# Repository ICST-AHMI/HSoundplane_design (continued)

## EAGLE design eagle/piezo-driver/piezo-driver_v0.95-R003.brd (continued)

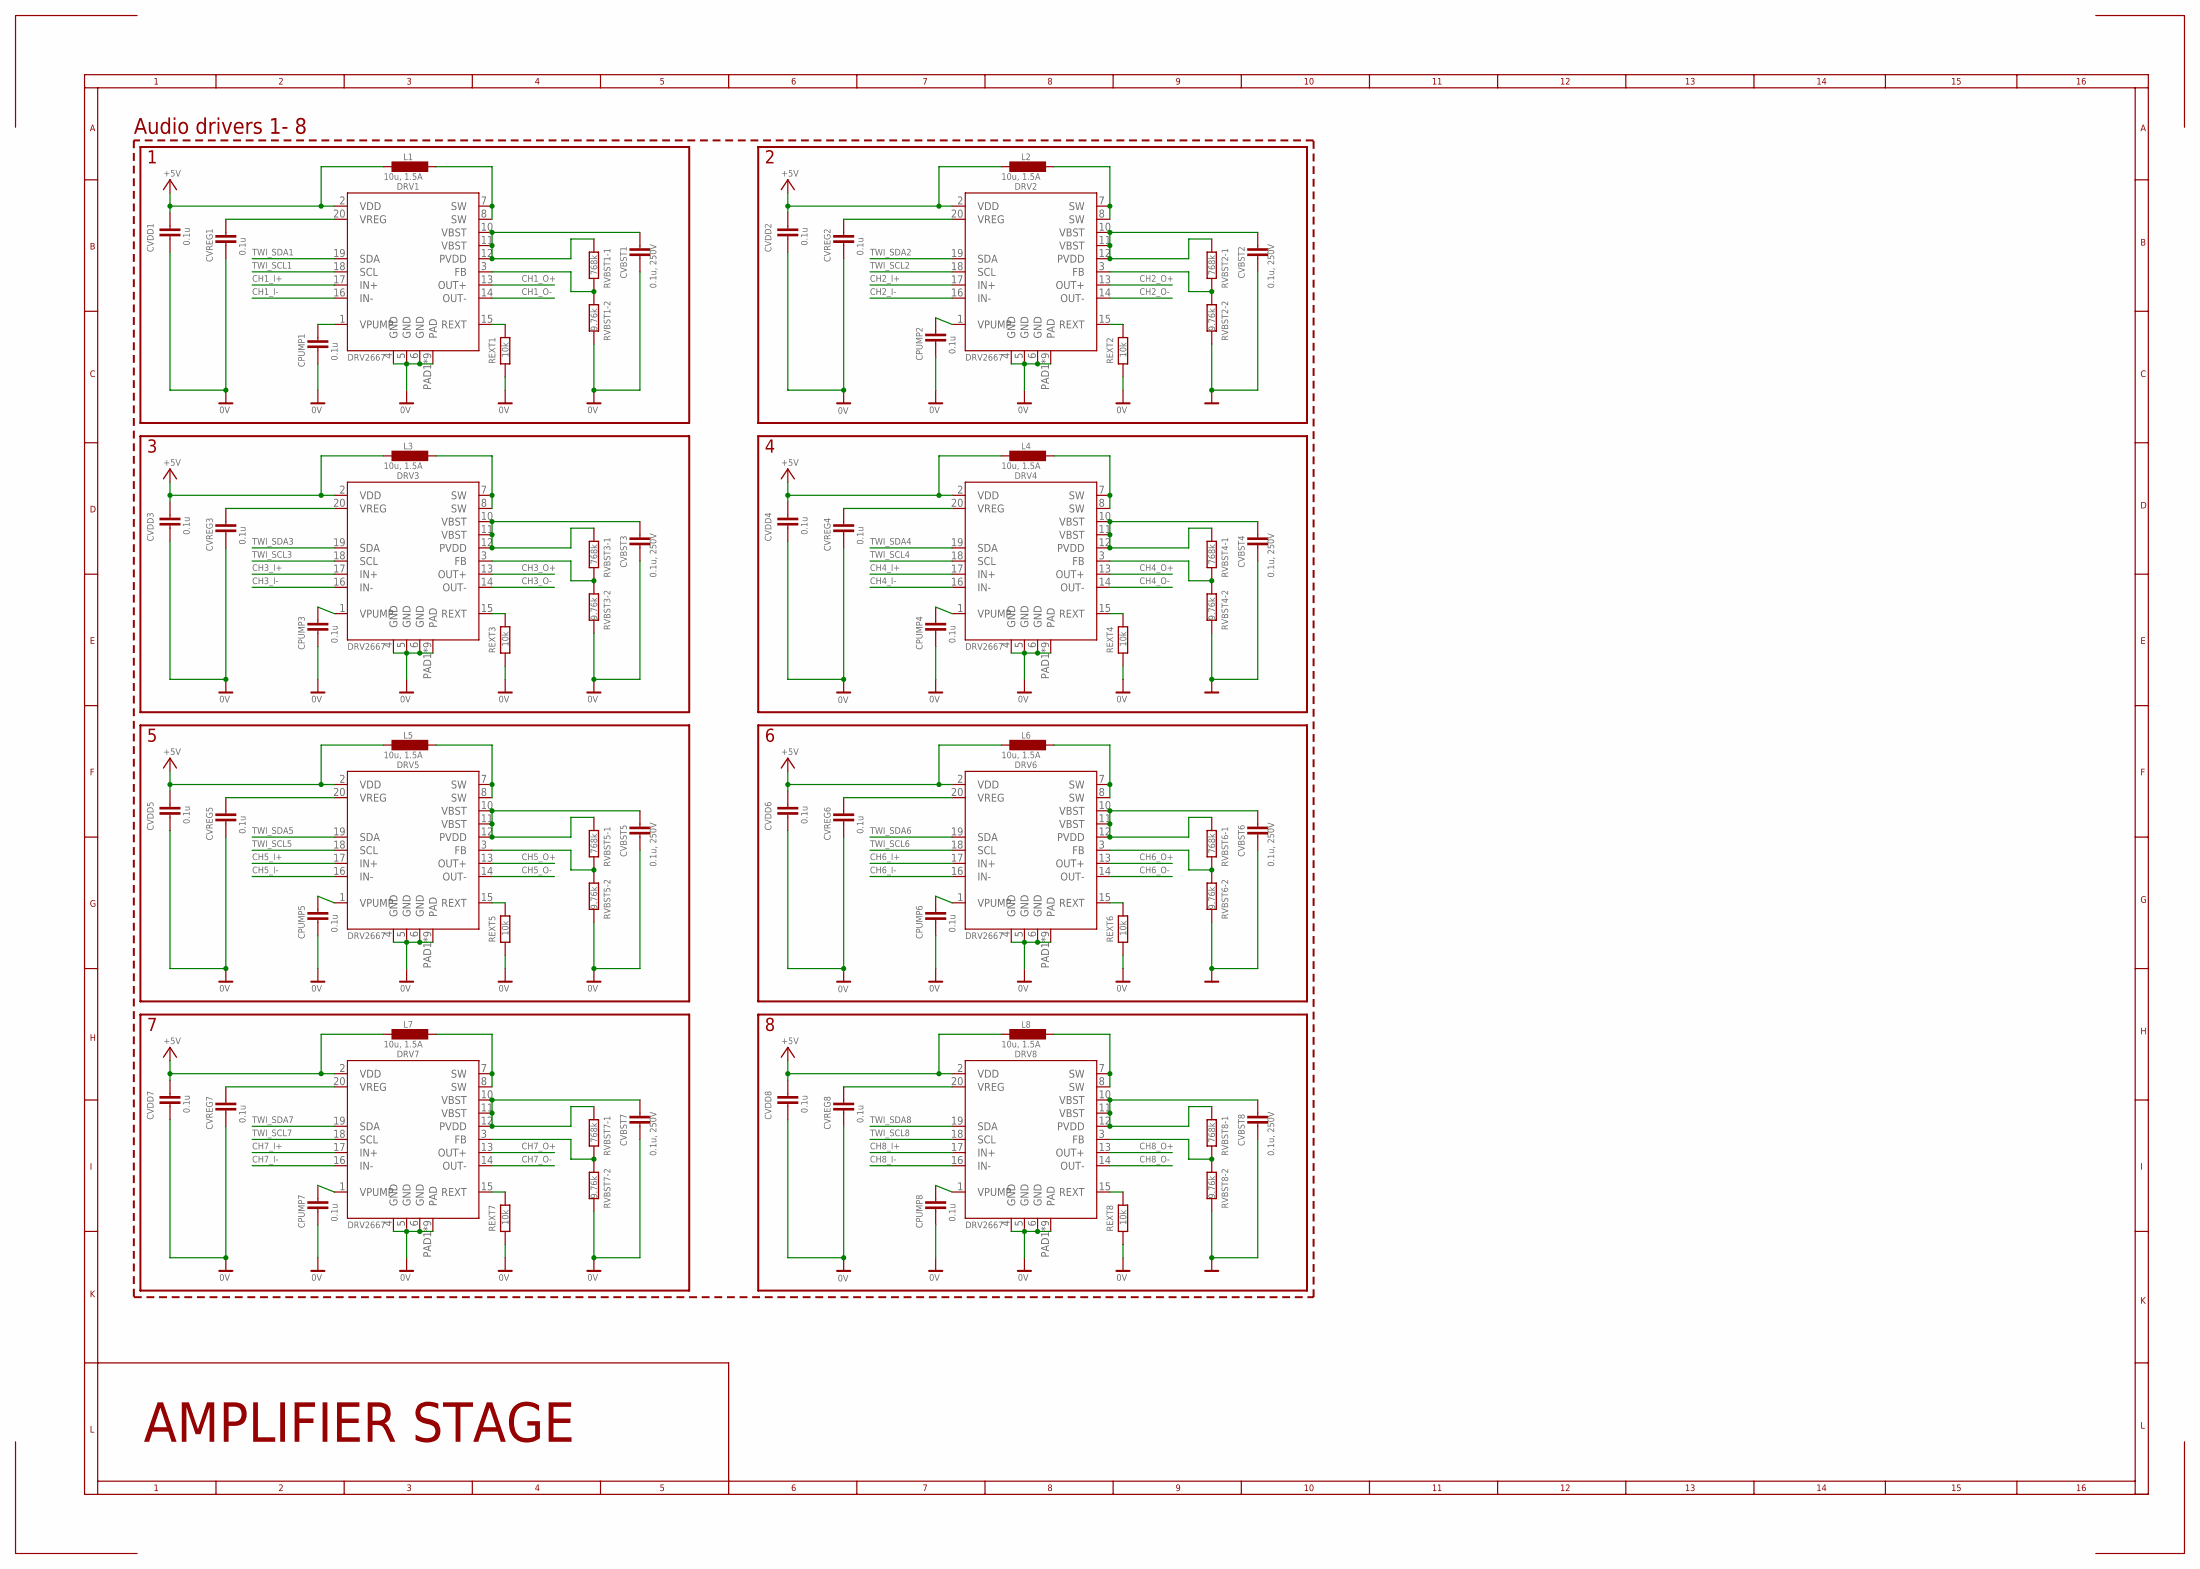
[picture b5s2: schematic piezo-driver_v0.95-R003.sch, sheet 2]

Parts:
CPUMP1, CPUMP2, CPUMP3, CPUMP4, CPUMP5, CPUMP6, CPUMP7, CPUMP8: 0.1u; C0402
CVBST1, CVBST2, CVBST3, CVBST4, CVBST5, CVBST6, CVBST7, CVBST8: 0.1u, 250V; C0805
CVDD1, CVDD2, CVDD3, CVDD4, CVDD5, CVDD6, CVDD7, CVDD8: 0.1u; C0402
CVREG1, CVREG2, CVREG3, CVREG4, CVREG5, CVREG6, CVREG7, CVREG8: 0.1u; C0402
DRV1, DRV2, DRV3, DRV4, DRV5, DRV6, DRV7, DRV8: DRV2667; QFN-20_9TH
L1, L2, L3, L4, L5, L6, L7, L8: 10u, 1.5A; L4.0X4.0
REXT1, REXT2, REXT3, REXT4, REXT5, REXT6, REXT7, REXT8: 10k; R0402
RVBST1-1, RVBST2-1, RVBST3-1, RVBST4-1, RVBST5-1, RVBST6-1, RVBST7-1, RVBST8-1: 768k; R0402
RVBST1-2, RVBST2-2, RVBST3-2, RVBST4-2, RVBST5-2, RVBST6-2, RVBST7-2, RVBST8-2: 9.76k; R0402

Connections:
0V: CPUMP1.2, CPUMP2.2, CPUMP3.2, CPUMP4.2, CPUMP5.2, CPUMP6.2, CPUMP7.2, CPUMP8.2, CVBST1.2, CVBST2.2, CVBST3.2, CVBST4.2, CVBST5.2, CVBST6.2, CVBST7.2, CVBST8.2, CVDD1.2, CVDD2.2, CVDD3.2, CVDD4.2, CVDD5.2, CVDD6.2, CVDD7.2, CVDD8.2, CVREG1.2, CVREG2.2, CVREG3.2, CVREG4.2, CVREG5.2, CVREG6.2, CVREG7.2, CVREG8.2, DRV1.4 (GND), DRV1.5 (GND), DRV1.6 (GND), DRV1.PAD1 (PAD), DRV1.PAD2 (PAD), DRV1.PAD3 (PAD), DRV1.PAD4 (PAD), DRV1.PAD5 (PAD), DRV1.PAD6 (PAD), DRV1.PAD7 (PAD), DRV1.PAD8 (PAD), DRV1.PAD9 (PAD), DRV2.4 (GND), DRV2.5 (GND), DRV2.6 (GND), DRV2.PAD1 (PAD), DRV2.PAD2 (PAD), DRV2.PAD3 (PAD), DRV2.PAD4 (PAD), DRV2.PAD5 (PAD), DRV2.PAD6 (PAD), DRV2.PAD7 (PAD), DRV2.PAD8 (PAD), DRV2.PAD9 (PAD), DRV3.4 (GND), DRV3.5 (GND), DRV3.6 (GND), DRV3.PAD1 (PAD), DRV3.PAD2 (PAD), DRV3.PAD3 (PAD), DRV3.PAD4 (PAD), DRV3.PAD5 (PAD), DRV3.PAD6 (PAD), DRV3.PAD7 (PAD), DRV3.PAD8 (PAD), DRV3.PAD9 (PAD), DRV4.4 (GND), DRV4.5 (GND), DRV4.6 (GND), DRV4.PAD1 (PAD), DRV4.PAD2 (PAD), DRV4.PAD3 (PAD), DRV4.PAD4 (PAD), DRV4.PAD5 (PAD), DRV4.PAD6 (PAD), DRV4.PAD7 (PAD), DRV4.PAD8 (PAD), DRV4.PAD9 (PAD), DRV5.4 (GND), DRV5.5 (GND), DRV5.6 (GND), DRV5.PAD1 (PAD), DRV5.PAD2 (PAD), DRV5.PAD3 (PAD), DRV5.PAD4 (PAD), DRV5.PAD5 (PAD), DRV5.PAD6 (PAD), DRV5.PAD7 (PAD), DRV5.PAD8 (PAD), DRV5.PAD9 (PAD), DRV6.4 (GND), DRV6.5 (GND), DRV6.6 (GND), DRV6.PAD1 (PAD), DRV6.PAD2 (PAD), DRV6.PAD3 (PAD), DRV6.PAD4 (PAD), DRV6.PAD5 (PAD), DRV6.PAD6 (PAD), DRV6.PAD7 (PAD), DRV6.PAD8 (PAD), DRV6.PAD9 (PAD), DRV7.4 (GND), DRV7.5 (GND), DRV7.6 (GND), DRV7.PAD1 (PAD), DRV7.PAD2 (PAD), DRV7.PAD3 (PAD), DRV7.PAD4 (PAD), DRV7.PAD5 (PAD), DRV7.PAD6 (PAD), DRV7.PAD7 (PAD), DRV7.PAD8 (PAD), DRV7.PAD9 (PAD), DRV8.4 (GND), DRV8.5 (GND), DRV8.6 (GND), DRV8.PAD1 (PAD), DRV8.PAD2 (PAD), DRV8.PAD3 (PAD), DRV8.PAD4 (PAD), DRV8.PAD5 (PAD), DRV8.PAD6 (PAD), DRV8.PAD7 (PAD), DRV8.PAD8 (PAD), DRV8.PAD9 (PAD), REXT1.1, REXT2.1, REXT3.1, REXT4.1, REXT5.1, REXT6.1, REXT7.1, REXT8.1, RVBST1-2.1, RVBST2-2.1, RVBST3-2.1, RVBST4-2.1, RVBST5-2.1, RVBST6-2.1, RVBST7-2.1, RVBST8-2.1; also elsewhere on the board
+5V: CVDD1.1, CVDD2.1, CVDD3.1, CVDD4.1, CVDD5.1, CVDD6.1, CVDD7.1, CVDD8.1, DRV1.2 (VDD), DRV2.2 (VDD), DRV3.2 (VDD), DRV4.2 (VDD), DRV5.2 (VDD), DRV6.2 (VDD), DRV7.2 (VDD), DRV8.2 (VDD), L1.2, L2.2, L3.2, L4.2, L5.2, L6.2, L7.2, L8.2; also elsewhere on the board
CH1_I+: DRV1.17 (IN+); also elsewhere on the board
CH1_I-: DRV1.16 (IN-); also elsewhere on the board
CH1_O+: DRV1.13 (OUT+); also elsewhere on the board
CH1_O-: DRV1.14 (OUT-); also elsewhere on the board
CH2_I+: DRV2.17 (IN+); also elsewhere on the board
CH2_I-: DRV2.16 (IN-); also elsewhere on the board
CH2_O+: DRV2.13 (OUT+); also elsewhere on the board
CH2_O-: DRV2.14 (OUT-); also elsewhere on the board
CH3_I+: DRV3.17 (IN+); also elsewhere on the board
CH3_I-: DRV3.16 (IN-); also elsewhere on the board
CH3_O+: DRV3.13 (OUT+); also elsewhere on the board
CH3_O-: DRV3.14 (OUT-); also elsewhere on the board
CH4_I+: DRV4.17 (IN+); also elsewhere on the board
CH4_I-: DRV4.16 (IN-); also elsewhere on the board
CH4_O+: DRV4.13 (OUT+); also elsewhere on the board
CH4_O-: DRV4.14 (OUT-); also elsewhere on the board
CH5_I+: DRV5.17 (IN+); also elsewhere on the board
CH5_I-: DRV5.16 (IN-); also elsewhere on the board
CH5_O+: DRV5.13 (OUT+); also elsewhere on the board
CH5_O-: DRV5.14 (OUT-); also elsewhere on the board
CH6_I+: DRV6.17 (IN+); also elsewhere on the board
CH6_I-: DRV6.16 (IN-); also elsewhere on the board
CH6_O+: DRV6.13 (OUT+); also elsewhere on the board
CH6_O-: DRV6.14 (OUT-); also elsewhere on the board
CH7_I+: DRV7.17 (IN+); also elsewhere on the board
CH7_I-: DRV7.16 (IN-); also elsewhere on the board
CH7_O+: DRV7.13 (OUT+); also elsewhere on the board
CH7_O-: DRV7.14 (OUT-); also elsewhere on the board
CH8_I+: DRV8.17 (IN+); also elsewhere on the board
CH8_I-: DRV8.16 (IN-); also elsewhere on the board
CH8_O+: DRV8.13 (OUT+); also elsewhere on the board
CH8_O-: DRV8.14 (OUT-); also elsewhere on the board
CVBST1: CVBST1.1, DRV1.10 (VBST), DRV1.11 (VBST), DRV1.12 (PVDD), RVBST1-1.2
CVBST2: CVBST2.1, DRV2.10 (VBST), DRV2.11 (VBST), DRV2.12 (PVDD), RVBST2-1.2
CVBST3: CVBST3.1, DRV3.10 (VBST), DRV3.11 (VBST), DRV3.12 (PVDD), RVBST3-1.2
CVBST4: CVBST4.1, DRV4.10 (VBST), DRV4.11 (VBST), DRV4.12 (PVDD), RVBST4-1.2
CVBST5: CVBST5.1, DRV5.10 (VBST), DRV5.11 (VBST), DRV5.12 (PVDD), RVBST5-1.2
CVBST6: CVBST6.1, DRV6.10 (VBST), DRV6.11 (VBST), DRV6.12 (PVDD), RVBST6-1.2
CVBST7: CVBST7.1, DRV7.10 (VBST), DRV7.11 (VBST), DRV7.12 (PVDD), RVBST7-1.2
CVBST8: CVBST8.1, DRV8.10 (VBST), DRV8.11 (VBST), DRV8.12 (PVDD), RVBST8-1.2
L1: DRV1.7 (SW), DRV1.8 (SW), L1.1
L2: DRV2.7 (SW), DRV2.8 (SW), L2.1
L3: DRV3.7 (SW), DRV3.8 (SW), L3.1
L4: DRV4.7 (SW), DRV4.8 (SW), L4.1
L5: DRV5.7 (SW), DRV5.8 (SW), L5.1
L6: DRV6.7 (SW), DRV6.8 (SW), L6.1
L7: DRV7.7 (SW), DRV7.8 (SW), L7.1
L8: DRV8.7 (SW), DRV8.8 (SW), L8.1
unnamed: DRV1.3 (FB), RVBST1-1.1, RVBST1-2.2
unnamed: DRV1.15 (REXT), REXT1.2
unnamed: CPUMP1.1, DRV1.1 (VPUMP)
unnamed: CVREG1.1, DRV1.20 (VREG)
unnamed: DRV3.3 (FB), RVBST3-1.1, RVBST3-2.2
unnamed: DRV3.15 (REXT), REXT3.2
unnamed: CPUMP3.1, DRV3.1 (VPUMP)
unnamed: CVREG3.1, DRV3.20 (VREG)
unnamed: DRV4.3 (FB), RVBST4-1.1, RVBST4-2.2
unnamed: DRV4.15 (REXT), REXT4.2
unnamed: CPUMP4.1, DRV4.1 (VPUMP)
unnamed: CVREG4.1, DRV4.20 (VREG)
unnamed: DRV2.3 (FB), RVBST2-1.1, RVBST2-2.2
unnamed: DRV2.15 (REXT), REXT2.2
unnamed: CPUMP2.1, DRV2.1 (VPUMP)
unnamed: CVREG2.1, DRV2.20 (VREG)
unnamed: DRV5.3 (FB), RVBST5-1.1, RVBST5-2.2
unnamed: DRV5.15 (REXT), REXT5.2
unnamed: CPUMP5.1, DRV5.1 (VPUMP)
unnamed: CVREG5.1, DRV5.20 (VREG)
unnamed: DRV6.3 (FB), RVBST6-1.1, RVBST6-2.2
unnamed: DRV6.15 (REXT), REXT6.2
unnamed: CPUMP6.1, DRV6.1 (VPUMP)
unnamed: CVREG6.1, DRV6.20 (VREG)
unnamed: DRV7.3 (FB), RVBST7-1.1, RVBST7-2.2
unnamed: DRV7.15 (REXT), REXT7.2
unnamed: CPUMP7.1, DRV7.1 (VPUMP)
unnamed: CVREG7.1, DRV7.20 (VREG)
unnamed: DRV8.3 (FB), RVBST8-1.1, RVBST8-2.2
unnamed: DRV8.15 (REXT), REXT8.2
unnamed: CPUMP8.1, DRV8.1 (VPUMP)
unnamed: CVREG8.1, DRV8.20 (VREG)
TWI_SCL1: DRV1.18 (SCL); also elsewhere on the board
TWI_SCL2: DRV2.18 (SCL); also elsewhere on the board
TWI_SCL3: DRV3.18 (SCL); also elsewhere on the board
TWI_SCL4: DRV4.18 (SCL); also elsewhere on the board
TWI_SCL5: DRV5.18 (SCL); also elsewhere on the board
TWI_SCL6: DRV6.18 (SCL); also elsewhere on the board
TWI_SCL7: DRV7.18 (SCL); also elsewhere on the board
TWI_SCL8: DRV8.18 (SCL); also elsewhere on the board
TWI_SDA1: DRV1.19 (SDA); also elsewhere on the board
TWI_SDA2: DRV2.19 (SDA); also elsewhere on the board
TWI_SDA3: DRV3.19 (SDA); also elsewhere on the board
TWI_SDA4: DRV4.19 (SDA); also elsewhere on the board
TWI_SDA5: DRV5.19 (SDA); also elsewhere on the board
TWI_SDA6: DRV6.19 (SDA); also elsewhere on the board
TWI_SDA7: DRV7.19 (SDA); also elsewhere on the board
TWI_SDA8: DRV8.19 (SDA); also elsewhere on the board

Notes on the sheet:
AMPLIFIER STAGE
Audio drivers 1- 8

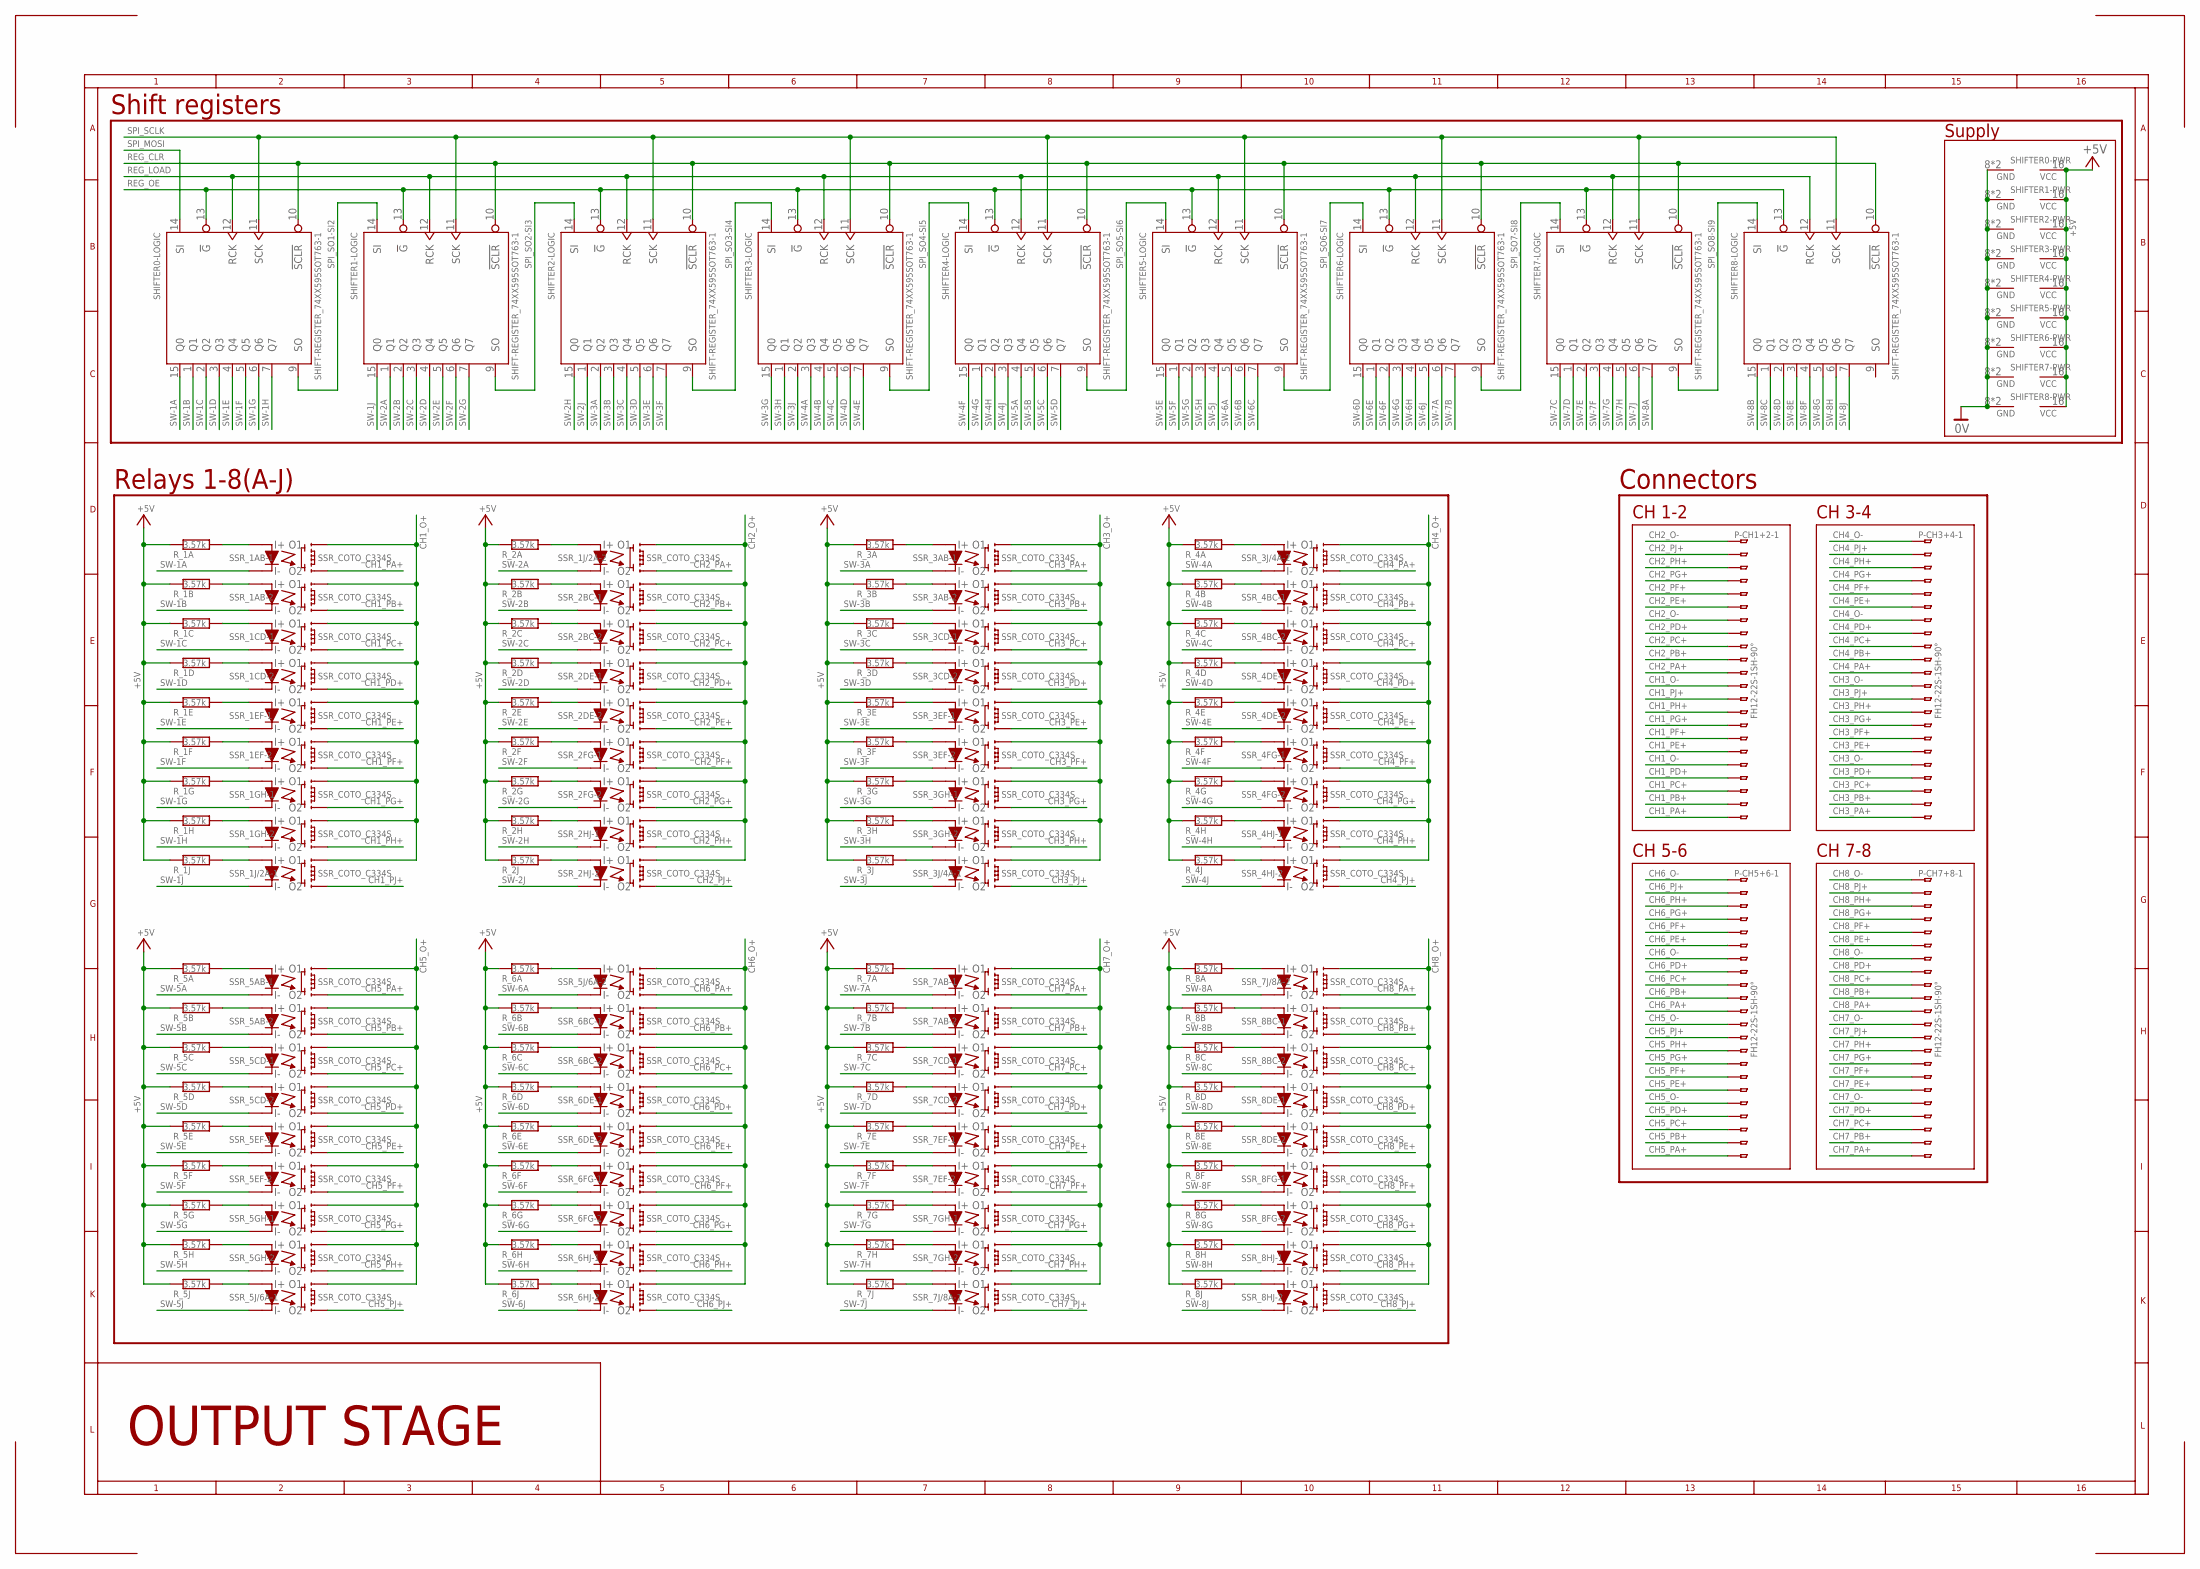
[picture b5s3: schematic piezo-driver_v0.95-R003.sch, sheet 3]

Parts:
P-CH1+2, P-CH3+4, P-CH5+6, P-CH7+8: FH12-22S-1SH-90°; FH12-22S-1SH
R_1A, R_1B, R_1C, R_1D, R_1E, R_1F, R_1G, R_1H, R_1J, R_2A, R_2B, R_2C, R_2D, R_2E, R_2F, R_2G, R_2H, R_2J, R_3A, R_3B, R_3C, R_3D, R_3E, R_3F, R_3G, R_3H, R_3J, R_4A, R_4B, R_4C, R_4D, R_4E, R_4F, R_4G, R_4H, R_4J, R_5A, R_5B, R_5C, R_5D, R_5E, R_5F, R_5G, R_5H, R_5J, R_6A, R_6B, R_6C, R_6D, R_6E, R_6F, R_6G, R_6H, R_6J, R_7A, R_7B, R_7C, R_7D, R_7E, R_7F, R_7G, R_7H, R_7J, R_8A, R_8B, R_8C, R_8D, R_8E, R_8F, R_8G, R_8H, R_8J: 3.57k; R0402
SHIFTER0, SHIFTER1, SHIFTER2, SHIFTER3, SHIFTER4, SHIFTER5, SHIFTER6, SHIFTER7, SHIFTER8: SHIFT-REGISTER_74XX595SOT763-1; SOT763-1
SSR_1AB, SSR_1CD, SSR_1EF, SSR_1GH, SSR_1J/2A, SSR_2BC, SSR_2DE, SSR_2FG, SSR_2HJ, SSR_3AB, SSR_3CD, SSR_3EF, SSR_3GH, SSR_3J/4A, SSR_4BC, SSR_4DE, SSR_4FG, SSR_4HJ, SSR_5AB, SSR_5CD, SSR_5EF, SSR_5GH, SSR_5J/6A, SSR_6BC, SSR_6DE, SSR_6FG, SSR_6HJ, SSR_7AB, SSR_7CD, SSR_7EF, SSR_7GH, SSR_7J/8A, SSR_8BC, SSR_8DE, SSR_8FG, SSR_8HJ: SSR_COTO_C334S; SOP8

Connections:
0V: SHIFTER0.8 (GND), SHIFTER0.PAD (GND), SHIFTER1.8 (GND), SHIFTER1.PAD (GND), SHIFTER2.8 (GND), SHIFTER2.PAD (GND), SHIFTER3.8 (GND), SHIFTER3.PAD (GND), SHIFTER4.8 (GND), SHIFTER4.PAD (GND), SHIFTER5.8 (GND), SHIFTER5.PAD (GND), SHIFTER6.8 (GND), SHIFTER6.PAD (GND), SHIFTER7.8 (GND), SHIFTER7.PAD (GND), SHIFTER8.8 (GND), SHIFTER8.PAD (GND); also elsewhere on the board
+5V: R_1A.2, R_1B.2, R_1C.2, R_1D.2, R_1E.2, R_1F.2, R_1G.2, R_1H.2, R_1J.2, R_2A.2, R_2B.2, R_2C.2, R_2D.2, R_2E.2, R_2F.2, R_2G.2, R_2H.2, R_2J.2, R_3A.2, R_3B.2, R_3C.2, R_3D.2, R_3E.2, R_3F.2, R_3G.2, R_3H.2, R_3J.2, R_4A.2, R_4B.2, R_4C.2, R_4D.2, R_4E.2, R_4F.2, R_4G.2, R_4H.2, R_4J.2, R_5A.2, R_5B.2, R_5C.2, R_5D.2, R_5E.2, R_5F.2, R_5G.2, R_5H.2, R_5J.2, R_6A.2, R_6B.2, R_6C.2, R_6D.2, R_6E.2, R_6F.2, R_6G.2, R_6H.2, R_6J.2, R_7A.2, R_7B.2, R_7C.2, R_7D.2, R_7E.2, R_7F.2, R_7G.2, R_7H.2, R_7J.2, R_8A.2, R_8B.2, R_8C.2, R_8D.2, R_8E.2, R_8F.2, R_8G.2, R_8H.2, R_8J.2, SHIFTER0.16 (VCC), SHIFTER1.16 (VCC), SHIFTER2.16 (VCC), SHIFTER3.16 (VCC), SHIFTER4.16 (VCC), SHIFTER5.16 (VCC), SHIFTER6.16 (VCC), SHIFTER7.16 (VCC), SHIFTER8.16 (VCC); also elsewhere on the board
CH1_O+: SSR_1AB.5 (O1), SSR_1AB.7 (O1), SSR_1CD.5 (O1), SSR_1CD.7 (O1), SSR_1EF.5 (O1), SSR_1EF.7 (O1), SSR_1GH.5 (O1), SSR_1GH.7 (O1), SSR_1J/2A.7 (O1); also elsewhere on the board
CH1_O-: P-CH1+2.12, P-CH1+2.18; also elsewhere on the board
CH1_PA+: P-CH1+2.22, SSR_1AB.8 (O2)
CH1_PB+: P-CH1+2.21, SSR_1AB.6 (O2)
CH1_PC+: P-CH1+2.20, SSR_1CD.8 (O2)
CH1_PD+: P-CH1+2.19, SSR_1CD.6 (O2)
CH1_PE+: P-CH1+2.17, SSR_1EF.8 (O2)
CH1_PF+: P-CH1+2.16, SSR_1EF.6 (O2)
CH1_PG+: P-CH1+2.15, SSR_1GH.8 (O2)
CH1_PH+: P-CH1+2.14, SSR_1GH.6 (O2)
CH1_PJ+: P-CH1+2.13, SSR_1J/2A.8 (O2)
CH2_O+: SSR_1J/2A.5 (O1), SSR_2BC.5 (O1), SSR_2BC.7 (O1), SSR_2DE.5 (O1), SSR_2DE.7 (O1), SSR_2FG.5 (O1), SSR_2FG.7 (O1), SSR_2HJ.5 (O1), SSR_2HJ.7 (O1); also elsewhere on the board
CH2_O-: P-CH1+2.1, P-CH1+2.7; also elsewhere on the board
CH2_PA+: P-CH1+2.11, SSR_1J/2A.6 (O2)
CH2_PB+: P-CH1+2.10, SSR_2BC.8 (O2)
CH2_PC+: P-CH1+2.9, SSR_2BC.6 (O2)
CH2_PD+: P-CH1+2.8, SSR_2DE.8 (O2)
CH2_PE+: P-CH1+2.6, SSR_2DE.6 (O2)
CH2_PF+: P-CH1+2.5, SSR_2FG.8 (O2)
CH2_PG+: P-CH1+2.4, SSR_2FG.6 (O2)
CH2_PH+: P-CH1+2.3, SSR_2HJ.8 (O2)
CH2_PJ+: P-CH1+2.2, SSR_2HJ.6 (O2)
CH3_O+: SSR_3AB.5 (O1), SSR_3AB.7 (O1), SSR_3CD.5 (O1), SSR_3CD.7 (O1), SSR_3EF.5 (O1), SSR_3EF.7 (O1), SSR_3GH.5 (O1), SSR_3GH.7 (O1), SSR_3J/4A.7 (O1); also elsewhere on the board
CH3_O-: P-CH3+4.12, P-CH3+4.18; also elsewhere on the board
CH3_PA+: P-CH3+4.22, SSR_3AB.8 (O2)
CH3_PB+: P-CH3+4.21, SSR_3AB.6 (O2)
CH3_PC+: P-CH3+4.20, SSR_3CD.8 (O2)
CH3_PD+: P-CH3+4.19, SSR_3CD.6 (O2)
CH3_PE+: P-CH3+4.17, SSR_3EF.8 (O2)
CH3_PF+: P-CH3+4.16, SSR_3EF.6 (O2)
CH3_PG+: P-CH3+4.15, SSR_3GH.8 (O2)
CH3_PH+: P-CH3+4.14, SSR_3GH.6 (O2)
CH3_PJ+: P-CH3+4.13, SSR_3J/4A.8 (O2)
CH4_O+: SSR_3J/4A.5 (O1), SSR_4BC.5 (O1), SSR_4BC.7 (O1), SSR_4DE.5 (O1), SSR_4DE.7 (O1), SSR_4FG.5 (O1), SSR_4FG.7 (O1), SSR_4HJ.5 (O1), SSR_4HJ.7 (O1); also elsewhere on the board
CH4_O-: P-CH3+4.1, P-CH3+4.7; also elsewhere on the board
CH4_PA+: P-CH3+4.11, SSR_3J/4A.6 (O2)
CH4_PB+: P-CH3+4.10, SSR_4BC.8 (O2)
CH4_PC+: P-CH3+4.9, SSR_4BC.6 (O2)
CH4_PD+: P-CH3+4.8, SSR_4DE.8 (O2)
CH4_PE+: P-CH3+4.6, SSR_4DE.6 (O2)
CH4_PF+: P-CH3+4.5, SSR_4FG.8 (O2)
CH4_PG+: P-CH3+4.4, SSR_4FG.6 (O2)
CH4_PH+: P-CH3+4.3, SSR_4HJ.8 (O2)
CH4_PJ+: P-CH3+4.2, SSR_4HJ.6 (O2)
CH5_O+: SSR_5AB.5 (O1), SSR_5AB.7 (O1), SSR_5CD.5 (O1), SSR_5CD.7 (O1), SSR_5EF.5 (O1), SSR_5EF.7 (O1), SSR_5GH.5 (O1), SSR_5GH.7 (O1), SSR_5J/6A.7 (O1); also elsewhere on the board
CH5_O-: P-CH5+6.12, P-CH5+6.18; also elsewhere on the board
CH5_PA+: P-CH5+6.22, SSR_5AB.8 (O2)
CH5_PB+: P-CH5+6.21, SSR_5AB.6 (O2)
CH5_PC+: P-CH5+6.20, SSR_5CD.8 (O2)
CH5_PD+: P-CH5+6.19, SSR_5CD.6 (O2)
CH5_PE+: P-CH5+6.17, SSR_5EF.8 (O2)
CH5_PF+: P-CH5+6.16, SSR_5EF.6 (O2)
CH5_PG+: P-CH5+6.15, SSR_5GH.8 (O2)
CH5_PH+: P-CH5+6.14, SSR_5GH.6 (O2)
CH5_PJ+: P-CH5+6.13, SSR_5J/6A.8 (O2)
CH6_O+: SSR_5J/6A.5 (O1), SSR_6BC.5 (O1), SSR_6BC.7 (O1), SSR_6DE.5 (O1), SSR_6DE.7 (O1), SSR_6FG.5 (O1), SSR_6FG.7 (O1), SSR_6HJ.5 (O1), SSR_6HJ.7 (O1); also elsewhere on the board
CH6_O-: P-CH5+6.1, P-CH5+6.7; also elsewhere on the board
CH6_PA+: P-CH5+6.11, SSR_5J/6A.6 (O2)
CH6_PB+: P-CH5+6.10, SSR_6BC.8 (O2)
CH6_PC+: P-CH5+6.9, SSR_6BC.6 (O2)
CH6_PD+: P-CH5+6.8, SSR_6DE.8 (O2)
CH6_PE+: P-CH5+6.6, SSR_6DE.6 (O2)
CH6_PF+: P-CH5+6.5, SSR_6FG.8 (O2)
CH6_PG+: P-CH5+6.4, SSR_6FG.6 (O2)
CH6_PH+: P-CH5+6.3, SSR_6HJ.8 (O2)
CH6_PJ+: P-CH5+6.2, SSR_6HJ.6 (O2)
CH7_O+: SSR_7AB.5 (O1), SSR_7AB.7 (O1), SSR_7CD.5 (O1), SSR_7CD.7 (O1), SSR_7EF.5 (O1), SSR_7EF.7 (O1), SSR_7GH.5 (O1), SSR_7GH.7 (O1), SSR_7J/8A.7 (O1); also elsewhere on the board
CH7_O-: P-CH7+8.12, P-CH7+8.18; also elsewhere on the board
CH7_PA+: P-CH7+8.22, SSR_7AB.8 (O2)
CH7_PB+: P-CH7+8.21, SSR_7AB.6 (O2)
CH7_PC+: P-CH7+8.20, SSR_7CD.8 (O2)
CH7_PD+: P-CH7+8.19, SSR_7CD.6 (O2)
CH7_PE+: P-CH7+8.17, SSR_7EF.8 (O2)
CH7_PF+: P-CH7+8.16, SSR_7EF.6 (O2)
CH7_PG+: P-CH7+8.15, SSR_7GH.8 (O2)
CH7_PH+: P-CH7+8.14, SSR_7GH.6 (O2)
CH7_PJ+: P-CH7+8.13, SSR_7J/8A.8 (O2)
CH8_O+: SSR_7J/8A.5 (O1), SSR_8BC.5 (O1), SSR_8BC.7 (O1), SSR_8DE.5 (O1), SSR_8DE.7 (O1), SSR_8FG.5 (O1), SSR_8FG.7 (O1), SSR_8HJ.5 (O1), SSR_8HJ.7 (O1); also elsewhere on the board
CH8_O-: P-CH7+8.1, P-CH7+8.7; also elsewhere on the board
CH8_PA+: P-CH7+8.11, SSR_7J/8A.6 (O2)
CH8_PB+: P-CH7+8.10, SSR_8BC.8 (O2)
CH8_PC+: P-CH7+8.9, SSR_8BC.6 (O2)
CH8_PD+: P-CH7+8.8, SSR_8DE.8 (O2)
CH8_PE+: P-CH7+8.6, SSR_8DE.6 (O2)
CH8_PF+: P-CH7+8.5, SSR_8FG.8 (O2)
CH8_PG+: P-CH7+8.4, SSR_8FG.6 (O2)
CH8_PH+: P-CH7+8.3, SSR_8HJ.8 (O2)
CH8_PJ+: P-CH7+8.2, SSR_8HJ.6 (O2)
unnamed: R_3A.1, SSR_3AB.1 (I+)
unnamed: R_3B.1, SSR_3AB.3 (I+)
unnamed: R_3C.1, SSR_3CD.1 (I+)
unnamed: R_3D.1, SSR_3CD.3 (I+)
unnamed: R_3E.1, SSR_3EF.1 (I+)
unnamed: R_3F.1, SSR_3EF.3 (I+)
unnamed: R_3G.1, SSR_3GH.1 (I+)
unnamed: R_3H.1, SSR_3GH.3 (I+)
unnamed: R_3J.1, SSR_3J/4A.1 (I+)
unnamed: R_4A.1, SSR_3J/4A.3 (I+)
unnamed: R_4B.1, SSR_4BC.1 (I+)
unnamed: R_4C.1, SSR_4BC.3 (I+)
unnamed: R_4D.1, SSR_4DE.1 (I+)
unnamed: R_4E.1, SSR_4DE.3 (I+)
unnamed: R_4F.1, SSR_4FG.1 (I+)
unnamed: R_4J.1, SSR_4HJ.3 (I+)
unnamed: R_4H.1, SSR_4HJ.1 (I+)
unnamed: R_4G.1, SSR_4FG.3 (I+)
unnamed: R_5A.1, SSR_5AB.1 (I+)
unnamed: R_5B.1, SSR_5AB.3 (I+)
unnamed: R_5C.1, SSR_5CD.1 (I+)
unnamed: R_5D.1, SSR_5CD.3 (I+)
unnamed: R_5E.1, SSR_5EF.1 (I+)
unnamed: R_5F.1, SSR_5EF.3 (I+)
unnamed: R_5G.1, SSR_5GH.1 (I+)
unnamed: R_5H.1, SSR_5GH.3 (I+)
unnamed: R_5J.1, SSR_5J/6A.1 (I+)
unnamed: R_6A.1, SSR_5J/6A.3 (I+)
unnamed: R_6B.1, SSR_6BC.1 (I+)
unnamed: R_6C.1, SSR_6BC.3 (I+)
unnamed: R_6D.1, SSR_6DE.1 (I+)
unnamed: R_6E.1, SSR_6DE.3 (I+)
unnamed: R_6F.1, SSR_6FG.1 (I+)
unnamed: R_6J.1, SSR_6HJ.3 (I+)
unnamed: R_6H.1, SSR_6HJ.1 (I+)
unnamed: R_6G.1, SSR_6FG.3 (I+)
unnamed: R_7A.1, SSR_7AB.1 (I+)
unnamed: R_7B.1, SSR_7AB.3 (I+)
unnamed: R_7C.1, SSR_7CD.1 (I+)
unnamed: R_7D.1, SSR_7CD.3 (I+)
unnamed: R_7E.1, SSR_7EF.1 (I+)
unnamed: R_1A.1, SSR_1AB.1 (I+)
unnamed: R_1B.1, SSR_1AB.3 (I+)
unnamed: R_7F.1, SSR_7EF.3 (I+)
unnamed: R_7G.1, SSR_7GH.1 (I+)
unnamed: R_1C.1, SSR_1CD.1 (I+)
unnamed: R_1D.1, SSR_1CD.3 (I+)
unnamed: R_1E.1, SSR_1EF.1 (I+)
unnamed: R_1F.1, SSR_1EF.3 (I+)
unnamed: R_1G.1, SSR_1GH.1 (I+)
unnamed: R_1H.1, SSR_1GH.3 (I+)
unnamed: R_1J.1, SSR_1J/2A.1 (I+)
unnamed: R_2A.1, SSR_1J/2A.3 (I+)
unnamed: R_2B.1, SSR_2BC.1 (I+)
unnamed: R_2C.1, SSR_2BC.3 (I+)
unnamed: R_7H.1, SSR_7GH.3 (I+)
unnamed: R_7J.1, SSR_7J/8A.1 (I+)
unnamed: R_8A.1, SSR_7J/8A.3 (I+)
unnamed: R_8B.1, SSR_8BC.1 (I+)
unnamed: R_8C.1, SSR_8BC.3 (I+)
unnamed: R_8D.1, SSR_8DE.1 (I+)
unnamed: R_8E.1, SSR_8DE.3 (I+)
unnamed: R_8F.1, SSR_8FG.1 (I+)
unnamed: R_8J.1, SSR_8HJ.3 (I+)
unnamed: R_2D.1, SSR_2DE.1 (I+)
unnamed: R_2E.1, SSR_2DE.3 (I+)
unnamed: R_2F.1, SSR_2FG.1 (I+)
unnamed: R_2J.1, SSR_2HJ.3 (I+)
unnamed: R_2H.1, SSR_2HJ.1 (I+)
unnamed: R_2G.1, SSR_2FG.3 (I+)
unnamed: R_8H.1, SSR_8HJ.1 (I+)
unnamed: R_8G.1, SSR_8FG.3 (I+)
REG_CLR: SHIFTER0.10 (!SCLR), SHIFTER1.10 (!SCLR), SHIFTER2.10 (!SCLR), SHIFTER3.10 (!SCLR), SHIFTER4.10 (!SCLR), SHIFTER5.10 (!SCLR), SHIFTER6.10 (!SCLR), SHIFTER7.10 (!SCLR), SHIFTER8.10 (!SCLR); also elsewhere on the board
REG_LOAD: SHIFTER0.12 (RCK), SHIFTER1.12 (RCK), SHIFTER2.12 (RCK), SHIFTER3.12 (RCK), SHIFTER4.12 (RCK), SHIFTER5.12 (RCK), SHIFTER6.12 (RCK), SHIFTER7.12 (RCK), SHIFTER8.12 (RCK); also elsewhere on the board
REG_OE: SHIFTER0.13 (!G), SHIFTER1.13 (!G), SHIFTER2.13 (!G), SHIFTER3.13 (!G), SHIFTER4.13 (!G), SHIFTER5.13 (!G), SHIFTER6.13 (!G), SHIFTER7.13 (!G), SHIFTER8.13 (!G); also elsewhere on the board
SPI_MOSI: SHIFTER0.14 (SI); also elsewhere on the board
SPI_SCLK: SHIFTER0.11 (SCK), SHIFTER1.11 (SCK), SHIFTER2.11 (SCK), SHIFTER3.11 (SCK), SHIFTER4.11 (SCK), SHIFTER5.11 (SCK), SHIFTER6.11 (SCK), SHIFTER7.11 (SCK), SHIFTER8.11 (SCK); also elsewhere on the board
SPI_SO1-SI2: SHIFTER0.9 (SO), SHIFTER1.14 (SI)
SPI_SO2-SI3: SHIFTER1.9 (SO), SHIFTER2.14 (SI)
SPI_SO3-SI4: SHIFTER2.9 (SO), SHIFTER3.14 (SI)
SPI_SO4-SI5: SHIFTER3.9 (SO), SHIFTER4.14 (SI)
SPI_SO5-SI6: SHIFTER4.9 (SO), SHIFTER5.14 (SI)
SPI_SO6-SI7: SHIFTER5.9 (SO), SHIFTER6.14 (SI)
SPI_SO7-SI8: SHIFTER6.9 (SO), SHIFTER7.14 (SI)
SPI_SO8-SI9: SHIFTER7.9 (SO), SHIFTER8.14 (SI)
SW-1A: SHIFTER0.15 (Q0), SSR_1AB.2 (I-)
SW-1B: SHIFTER0.1 (Q1), SSR_1AB.4 (I-)
SW-1C: SHIFTER0.2 (Q2), SSR_1CD.2 (I-)
SW-1D: SHIFTER0.3 (Q3), SSR_1CD.4 (I-)
SW-1E: SHIFTER0.4 (Q4), SSR_1EF.2 (I-)
SW-1F: SHIFTER0.5 (Q5), SSR_1EF.4 (I-)
SW-1G: SHIFTER0.6 (Q6), SSR_1GH.2 (I-)
SW-1H: SHIFTER0.7 (Q7), SSR_1GH.4 (I-)
SW-1J: SHIFTER1.15 (Q0), SSR_1J/2A.2 (I-)
SW-2A: SHIFTER1.1 (Q1), SSR_1J/2A.4 (I-)
SW-2B: SHIFTER1.2 (Q2), SSR_2BC.2 (I-)
SW-2C: SHIFTER1.3 (Q3), SSR_2BC.4 (I-)
SW-2D: SHIFTER1.4 (Q4), SSR_2DE.2 (I-)
SW-2E: SHIFTER1.5 (Q5), SSR_2DE.4 (I-)
SW-2F: SHIFTER1.6 (Q6), SSR_2FG.2 (I-)
SW-2G: SHIFTER1.7 (Q7), SSR_2FG.4 (I-)
SW-2H: SHIFTER2.15 (Q0), SSR_2HJ.2 (I-)
SW-2J: SHIFTER2.1 (Q1), SSR_2HJ.4 (I-)
SW-3A: SHIFTER2.2 (Q2), SSR_3AB.2 (I-)
SW-3B: SHIFTER2.3 (Q3), SSR_3AB.4 (I-)
SW-3C: SHIFTER2.4 (Q4), SSR_3CD.2 (I-)
SW-3D: SHIFTER2.5 (Q5), SSR_3CD.4 (I-)
SW-3E: SHIFTER2.6 (Q6), SSR_3EF.2 (I-)
SW-3F: SHIFTER2.7 (Q7), SSR_3EF.4 (I-)
SW-3G: SHIFTER3.15 (Q0), SSR_3GH.2 (I-)
SW-3H: SHIFTER3.1 (Q1), SSR_3GH.4 (I-)
SW-3J: SHIFTER3.2 (Q2), SSR_3J/4A.2 (I-)
SW-4A: SHIFTER3.3 (Q3), SSR_3J/4A.4 (I-)
SW-4B: SHIFTER3.4 (Q4), SSR_4BC.2 (I-)
SW-4C: SHIFTER3.5 (Q5), SSR_4BC.4 (I-)
SW-4D: SHIFTER3.6 (Q6), SSR_4DE.2 (I-)
SW-4E: SHIFTER3.7 (Q7), SSR_4DE.4 (I-)
SW-4F: SHIFTER4.15 (Q0), SSR_4FG.2 (I-)
SW-4G: SHIFTER4.1 (Q1), SSR_4FG.4 (I-)
SW-4H: SHIFTER4.2 (Q2), SSR_4HJ.2 (I-)
SW-4J: SHIFTER4.3 (Q3), SSR_4HJ.4 (I-)
SW-5A: SHIFTER4.4 (Q4), SSR_5AB.2 (I-)
SW-5B: SHIFTER4.5 (Q5), SSR_5AB.4 (I-)
SW-5C: SHIFTER4.6 (Q6), SSR_5CD.2 (I-)
SW-5D: SHIFTER4.7 (Q7), SSR_5CD.4 (I-)
SW-5E: SHIFTER5.15 (Q0), SSR_5EF.2 (I-)
SW-5F: SHIFTER5.1 (Q1), SSR_5EF.4 (I-)
SW-5G: SHIFTER5.2 (Q2), SSR_5GH.2 (I-)
SW-5H: SHIFTER5.3 (Q3), SSR_5GH.4 (I-)
SW-5J: SHIFTER5.4 (Q4), SSR_5J/6A.2 (I-)
SW-6A: SHIFTER5.5 (Q5), SSR_5J/6A.4 (I-)
SW-6B: SHIFTER5.6 (Q6), SSR_6BC.2 (I-)
SW-6C: SHIFTER5.7 (Q7), SSR_6BC.4 (I-)
SW-6D: SHIFTER6.15 (Q0), SSR_6DE.2 (I-)
SW-6E: SHIFTER6.1 (Q1), SSR_6DE.4 (I-)
SW-6F: SHIFTER6.2 (Q2), SSR_6FG.2 (I-)
SW-6G: SHIFTER6.3 (Q3), SSR_6FG.4 (I-)
SW-6H: SHIFTER6.4 (Q4), SSR_6HJ.2 (I-)
SW-6J: SHIFTER6.5 (Q5), SSR_6HJ.4 (I-)
SW-7A: SHIFTER6.6 (Q6), SSR_7AB.2 (I-)
SW-7B: SHIFTER6.7 (Q7), SSR_7AB.4 (I-)
SW-7C: SHIFTER7.15 (Q0), SSR_7CD.2 (I-)
SW-7D: SHIFTER7.1 (Q1), SSR_7CD.4 (I-)
SW-7E: SHIFTER7.2 (Q2), SSR_7EF.2 (I-)
SW-7F: SHIFTER7.3 (Q3), SSR_7EF.4 (I-)
SW-7G: SHIFTER7.4 (Q4), SSR_7GH.2 (I-)
SW-7H: SHIFTER7.5 (Q5), SSR_7GH.4 (I-)
SW-7J: SHIFTER7.6 (Q6), SSR_7J/8A.2 (I-)
SW-8A: SHIFTER7.7 (Q7), SSR_7J/8A.4 (I-)
SW-8B: SHIFTER8.15 (Q0), SSR_8BC.2 (I-)
SW-8C: SHIFTER8.1 (Q1), SSR_8BC.4 (I-)
SW-8D: SHIFTER8.2 (Q2), SSR_8DE.2 (I-)
SW-8E: SHIFTER8.3 (Q3), SSR_8DE.4 (I-)
SW-8F: SHIFTER8.4 (Q4), SSR_8FG.2 (I-)
SW-8G: SHIFTER8.5 (Q5), SSR_8FG.4 (I-)
SW-8H: SHIFTER8.6 (Q6), SSR_8HJ.2 (I-)
SW-8J: SHIFTER8.7 (Q7), SSR_8HJ.4 (I-)

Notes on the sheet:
OUTPUT STAGE
Relays 1-8(A-J)
Shift registers
Supply
Connectors
CH 1-2
CH 3-4
CH 5-6
CH 7-8

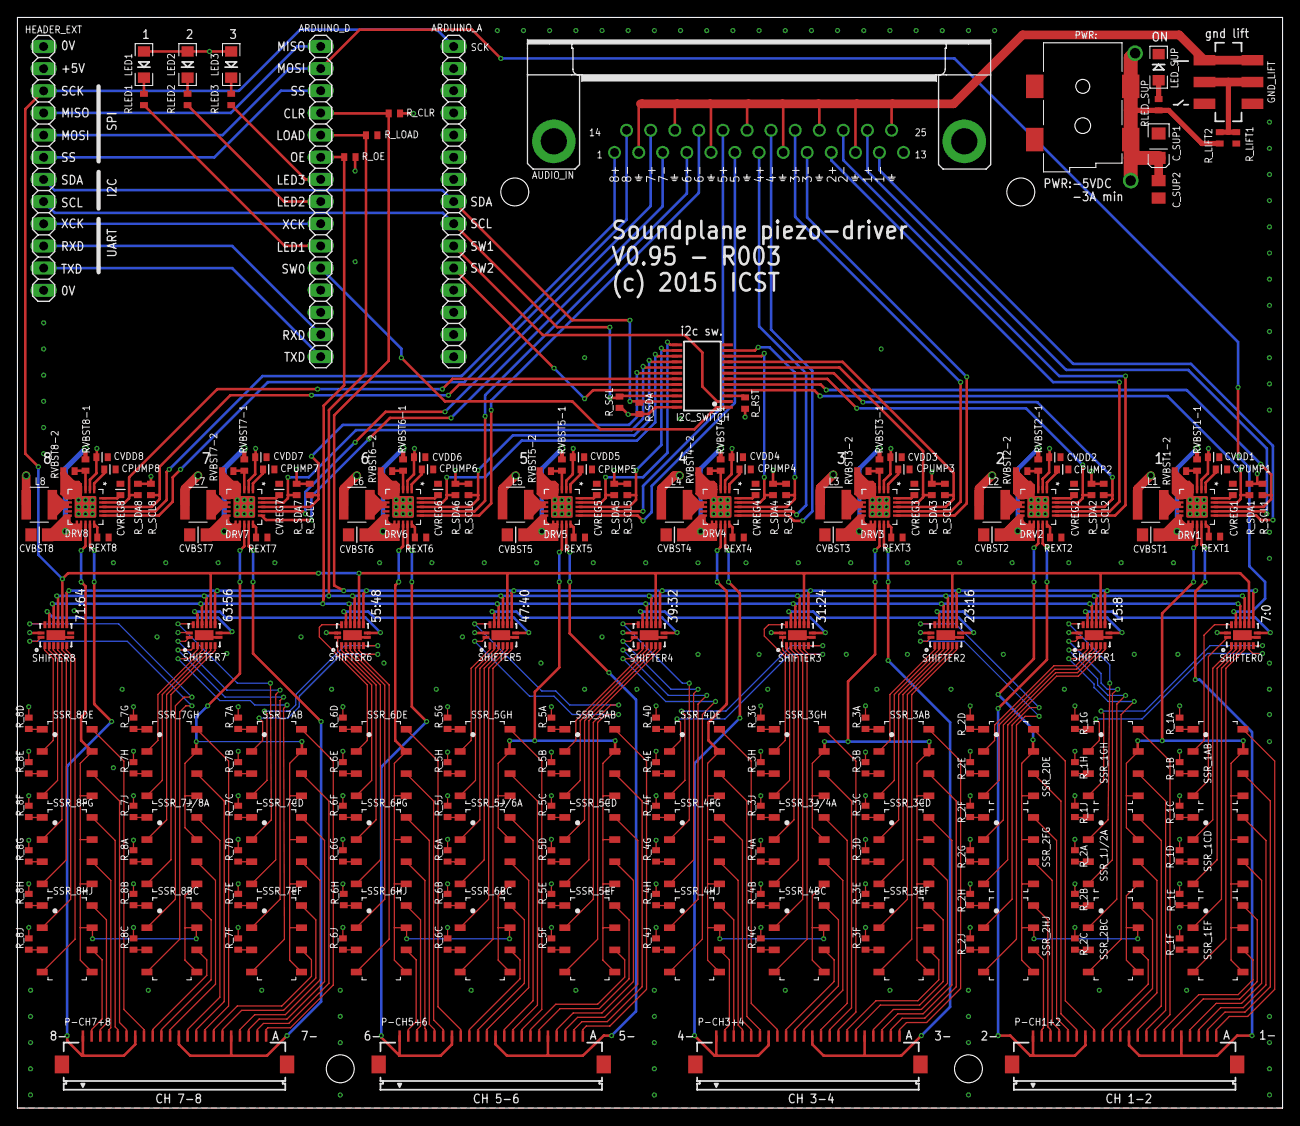
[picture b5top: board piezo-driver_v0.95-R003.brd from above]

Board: 4 copper layers, 145.0 x 125.0 mm, 234 parts (0 on the bottom side), 347 nets.
